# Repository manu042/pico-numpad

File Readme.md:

# PicoNumpad

Pico-based DIY numpad.

| Front | Back |
|---|---|
|  |  |

## Features

- Raspberry Pi Pico
- 17-key numpad layout
- 3 extra keys
- 2 rotary encoders
- LCD display

## Repository structure

```
pcb/          KiCad project (schematic and PCB)
pcb-layout/   FreeCAD layout model and exported board outline
```

### pcb-layout

A simple, parametric FreeCAD model of the numpad (PCB, keys, display,
Pico and encoders as basic boxes). It serves as a placement reference:
the board outline is exported as DXF and imported into KiCad as
`Edge.Cuts`, and the component positions are taken from the model.

## Tools

- KiCad
- FreeCAD

## Status

Work in progress. QMK Firmware and Case model will follow.

## License

See [LICENSE](LICENSE).

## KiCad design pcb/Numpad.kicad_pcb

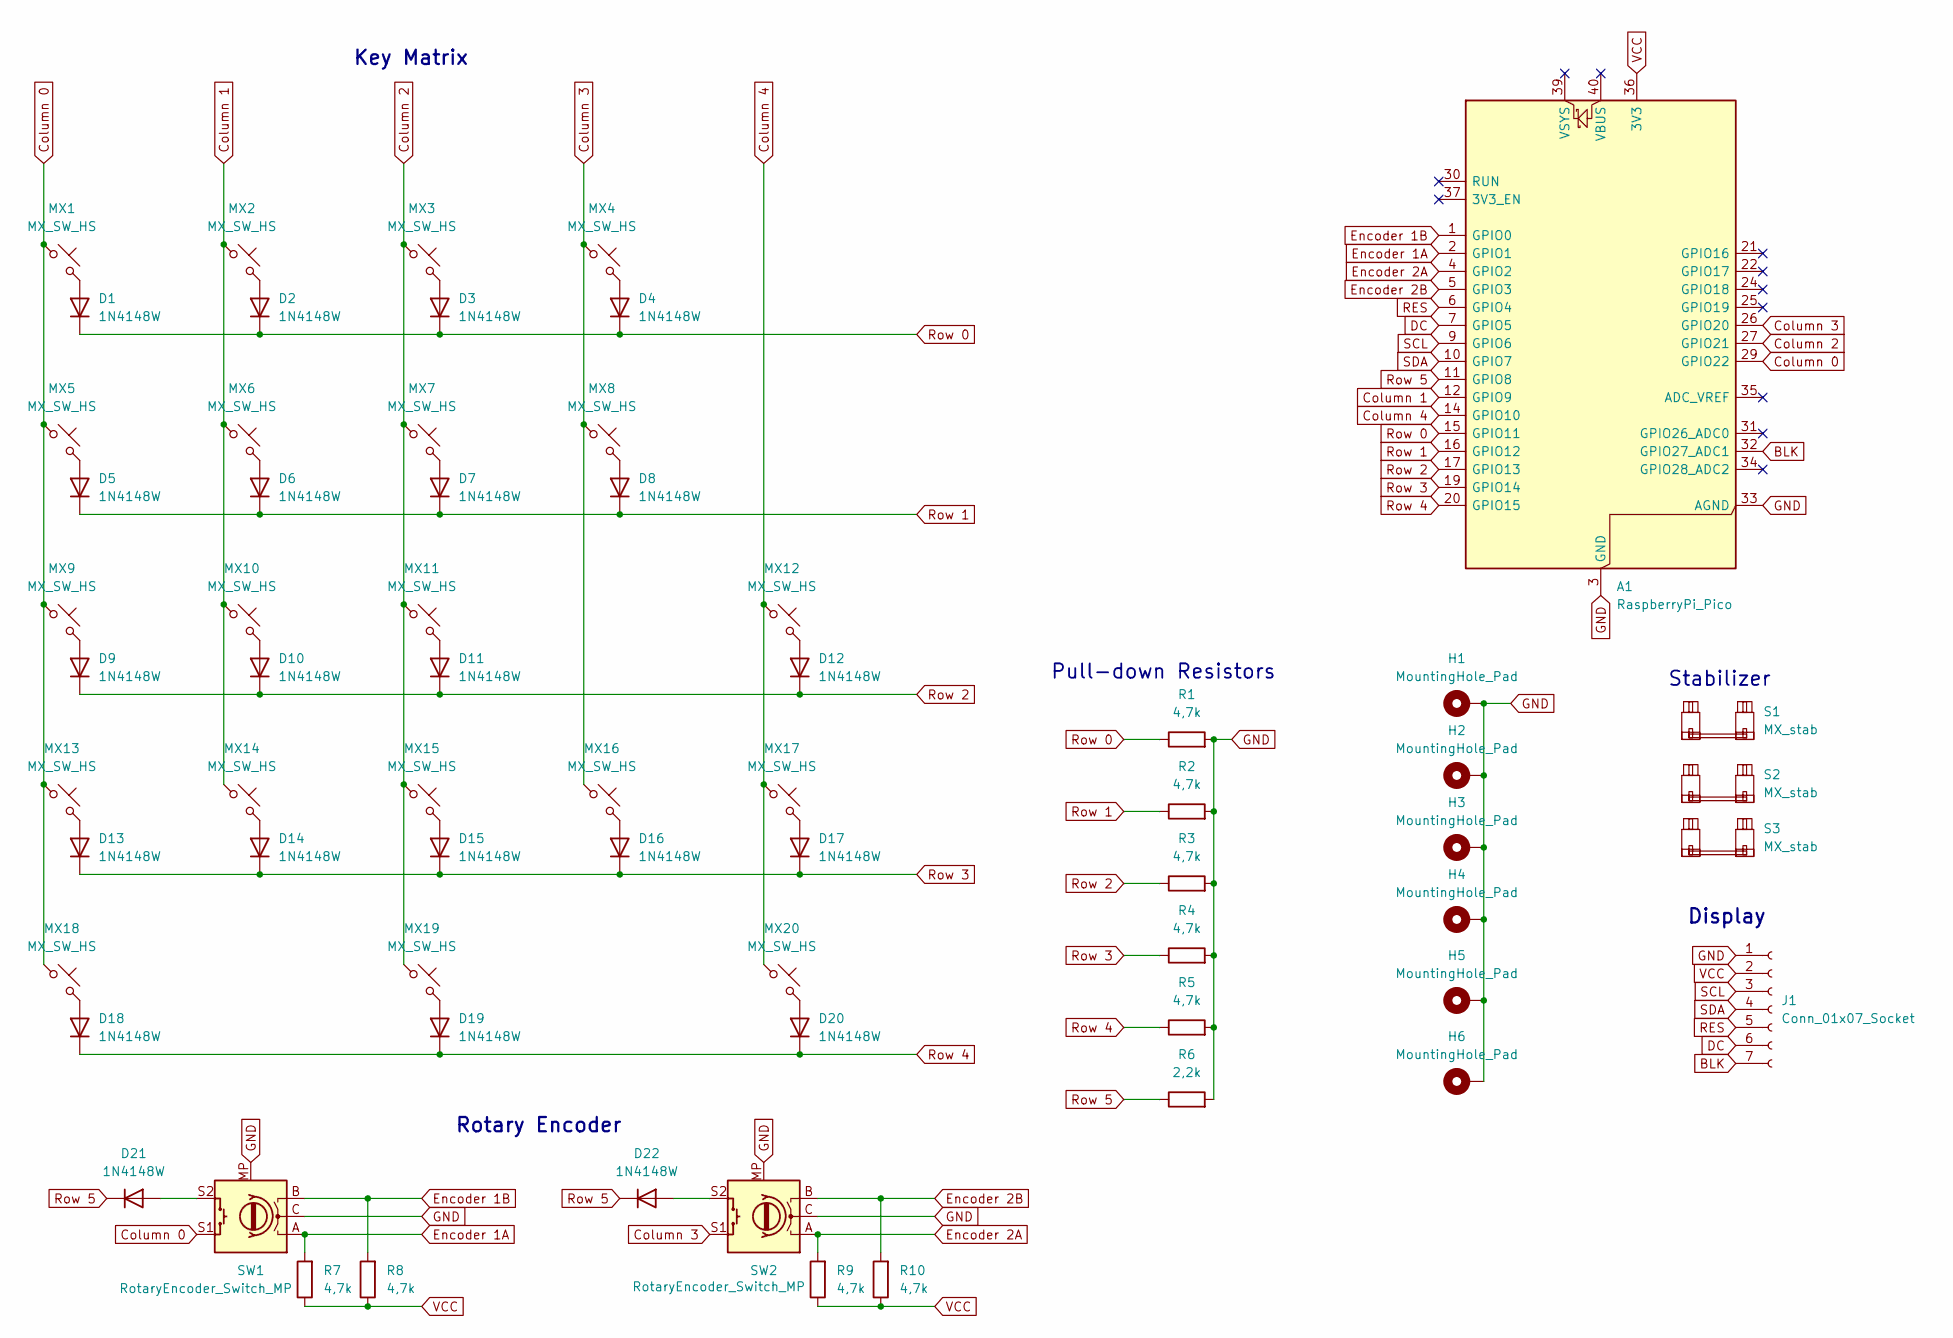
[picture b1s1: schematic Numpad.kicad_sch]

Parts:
A1: RaspberryPi_Pico; RaspberryPi_Pico_Common_Unspecified
D1, D2, D3, D4, D5, D6, D7, D8, D9, D10, D11, D12, D13, D14, D15, D16, D17, D18, D19, D20, D21, D22: 1N4148W; D_SOD-123; LCSC Part # 1N4148W
H1, H2, H3, H4, H5, H6: MountingHole_Pad; MountingHole_2.2mm_M2_Pad
J1: Conn_01x07_Socket; PinSocket_1x07_P2.54mm_Vertical
MX1, MX2, MX3, MX4, MX5, MX6, MX7, MX8, MX9, MX10, MX11, MX12, MX13, MX14, MX15, MX16, MX17, MX18, MX19, MX20: MX_SW_HS; SW_MX_HS_CPG151101S11_1u; LCSC Part # CPG151101S11-2
R1, R2, R3, R4, R5, R7, R8, R9, R10: 4,7k; R_0805_2012Metric_Pad1.20x1.40mm_HandSolder
R6: 2,2k; R_0805_2012Metric_Pad1.20x1.40mm_HandSolder
S1, S2, S3: MX_stab; STAB_MX_2u
SW1, SW2: RotaryEncoder_Switch_MP; RotaryEncoder_Alps_EC12E-Switch_Vertical_H20mm

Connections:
BLK: A1.32 (GPIO27_ADC1), J1.7
Column 0: A1.29 (GPIO22), MX1.1, MX5.1, MX9.1, MX13.1, MX18.1, SW1.S1
Column 1: A1.12 (GPIO9), MX2.1, MX6.1, MX10.1, MX14.1
Column 2: A1.27 (GPIO21), MX3.1, MX7.1, MX11.1, MX15.1, MX19.1
Column 3: A1.26 (GPIO20), MX4.1, MX8.1, MX16.1, SW2.S1
Column 4: A1.14 (GPIO10), MX12.1, MX17.1, MX20.1
DC: A1.7 (GPIO5), J1.6
Encoder 1A: A1.2 (GPIO1), R7.2, SW1.A
Encoder 1B: A1.1 (GPIO0), R8.2, SW1.B
Encoder 2A: A1.4 (GPIO2), R9.2, SW2.A
Encoder 2B: A1.5 (GPIO3), R10.2, SW2.B
GND: A1.3 (GND), A1.8 (GND), A1.13 (GND), A1.18 (GND), A1.23 (GND), A1.28 (GND), A1.33 (AGND), A1.38 (GND), H1.1 (1_1), H2.1 (1_1), H3.1 (1_1), H4.1 (1_1), H5.1 (1_1), H6.1 (1_1), J1.1, R1.2, R2.2, R3.2, R4.2, R5.2, R6.2, SW1.C, SW1.MP, SW2.C, SW2.MP
unnamed: D1.2 (A), MX1.2
unnamed: D2.2 (A), MX2.2
unnamed: D3.2 (A), MX3.2
unnamed: D4.2 (A), MX4.2
unnamed: D5.2 (A), MX5.2
unnamed: D6.2 (A), MX6.2
unnamed: D7.2 (A), MX7.2
unnamed: D8.2 (A), MX8.2
unnamed: D9.2 (A), MX9.2
unnamed: D10.2 (A), MX10.2
unnamed: D11.2 (A), MX11.2
unnamed: D12.2 (A), MX12.2
unnamed: D13.2 (A), MX13.2
unnamed: D14.2 (A), MX14.2
unnamed: D15.2 (A), MX15.2
unnamed: D16.2 (A), MX16.2
unnamed: D17.2 (A), MX17.2
unnamed: D18.2 (A), MX18.2
unnamed: D19.2 (A), MX19.2
unnamed: D20.2 (A), MX20.2
unnamed: D21.2 (A), SW1.S2
unnamed: D22.2 (A), SW2.S2
RES: A1.6 (GPIO4), J1.5
Row 0: A1.15 (GPIO11), D1.1 (K), D2.1 (K), D3.1 (K), D4.1 (K), R1.1
Row 1: A1.16 (GPIO12), D5.1 (K), D6.1 (K), D7.1 (K), D8.1 (K), R2.1
Row 2: A1.17 (GPIO13), D9.1 (K), D10.1 (K), D11.1 (K), D12.1 (K), R3.1
Row 3: A1.19 (GPIO14), D13.1 (K), D14.1 (K), D15.1 (K), D16.1 (K), D17.1 (K), R4.1
Row 4: A1.20 (GPIO15), D18.1 (K), D19.1 (K), D20.1 (K), R5.1
Row 5: A1.11 (GPIO8), D21.1 (K), D22.1 (K), R6.1
SCL: A1.9 (GPIO6), J1.3
SDA: A1.10 (GPIO7), J1.4
VCC: A1.36 (3V3), J1.2, R7.1, R8.1, R9.1, R10.1

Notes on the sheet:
Pull-down Resistors
Rotary Encoder
Display
Key Matrix
Stabilizer

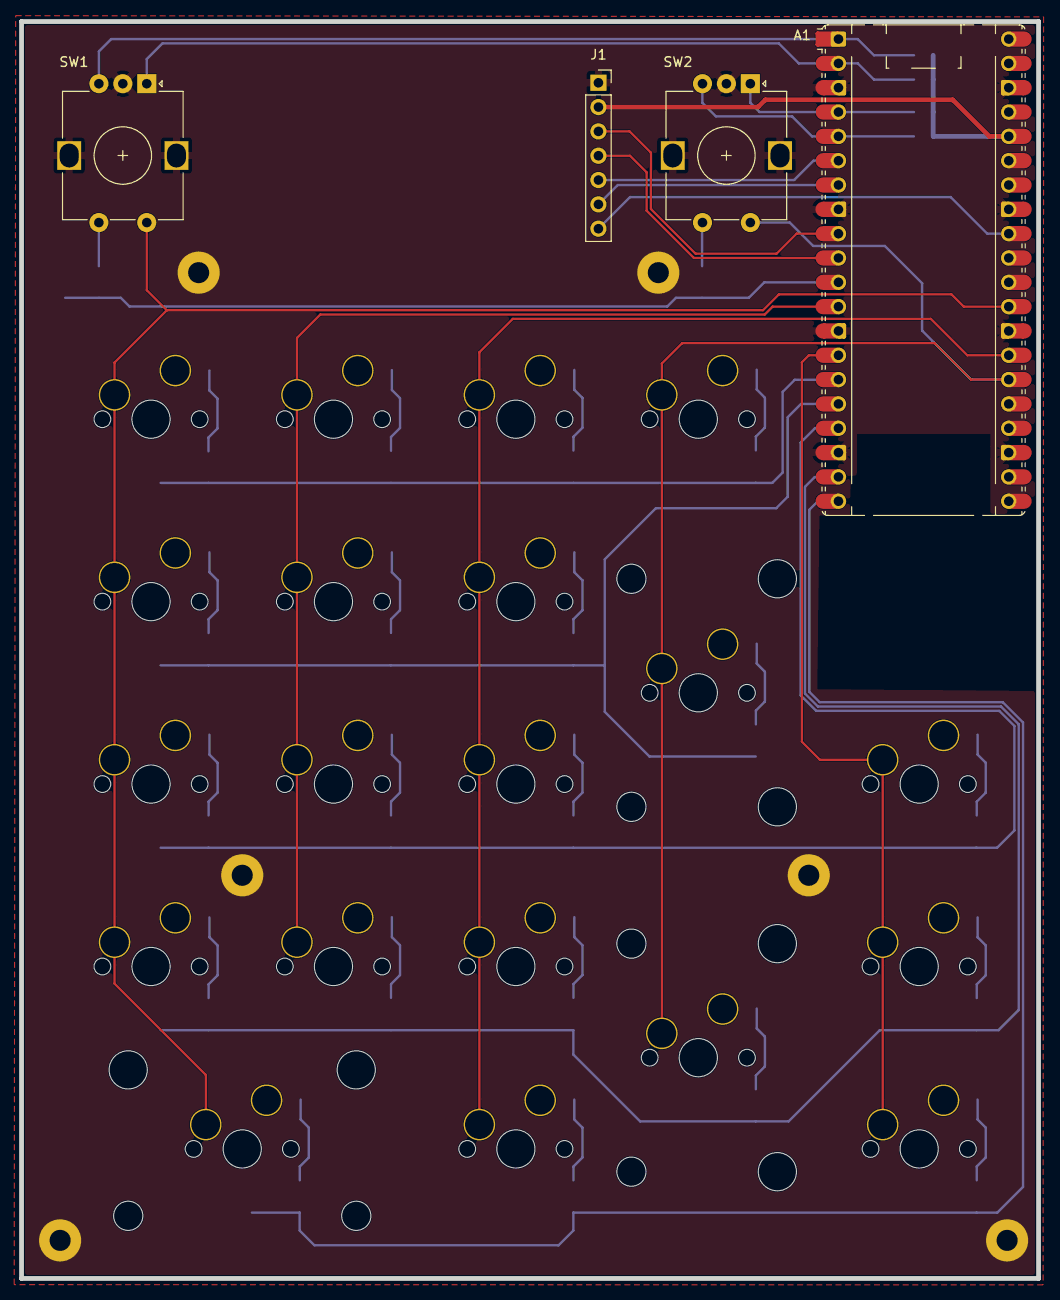
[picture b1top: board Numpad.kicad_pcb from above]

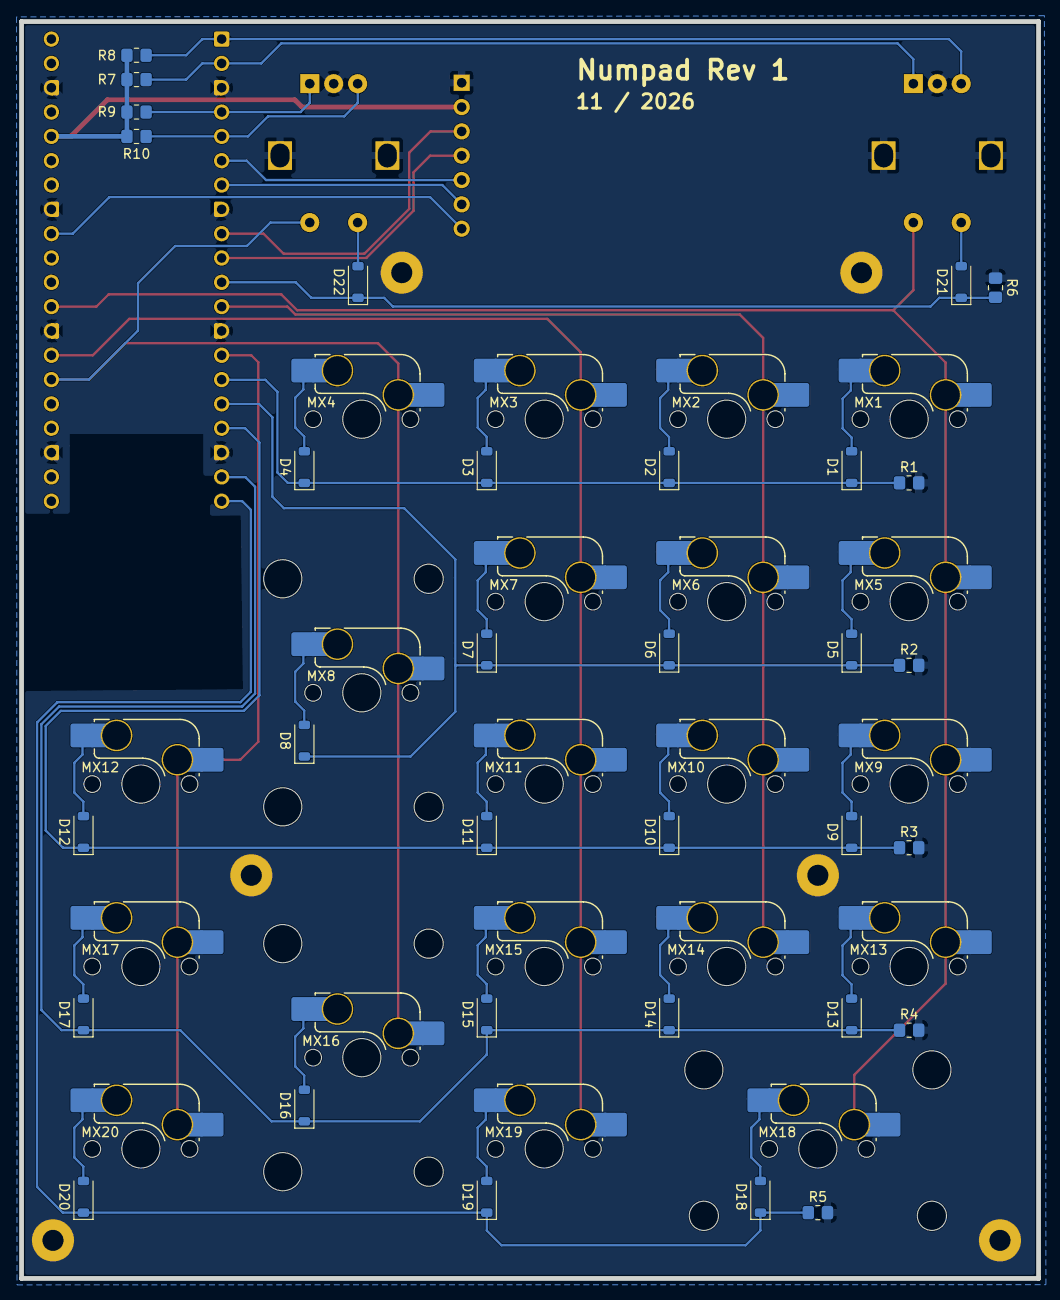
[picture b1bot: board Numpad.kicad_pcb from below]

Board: 2 copper layers, 106.2 x 131.2 mm, 65 parts (52 on the bottom side), 44 nets.
